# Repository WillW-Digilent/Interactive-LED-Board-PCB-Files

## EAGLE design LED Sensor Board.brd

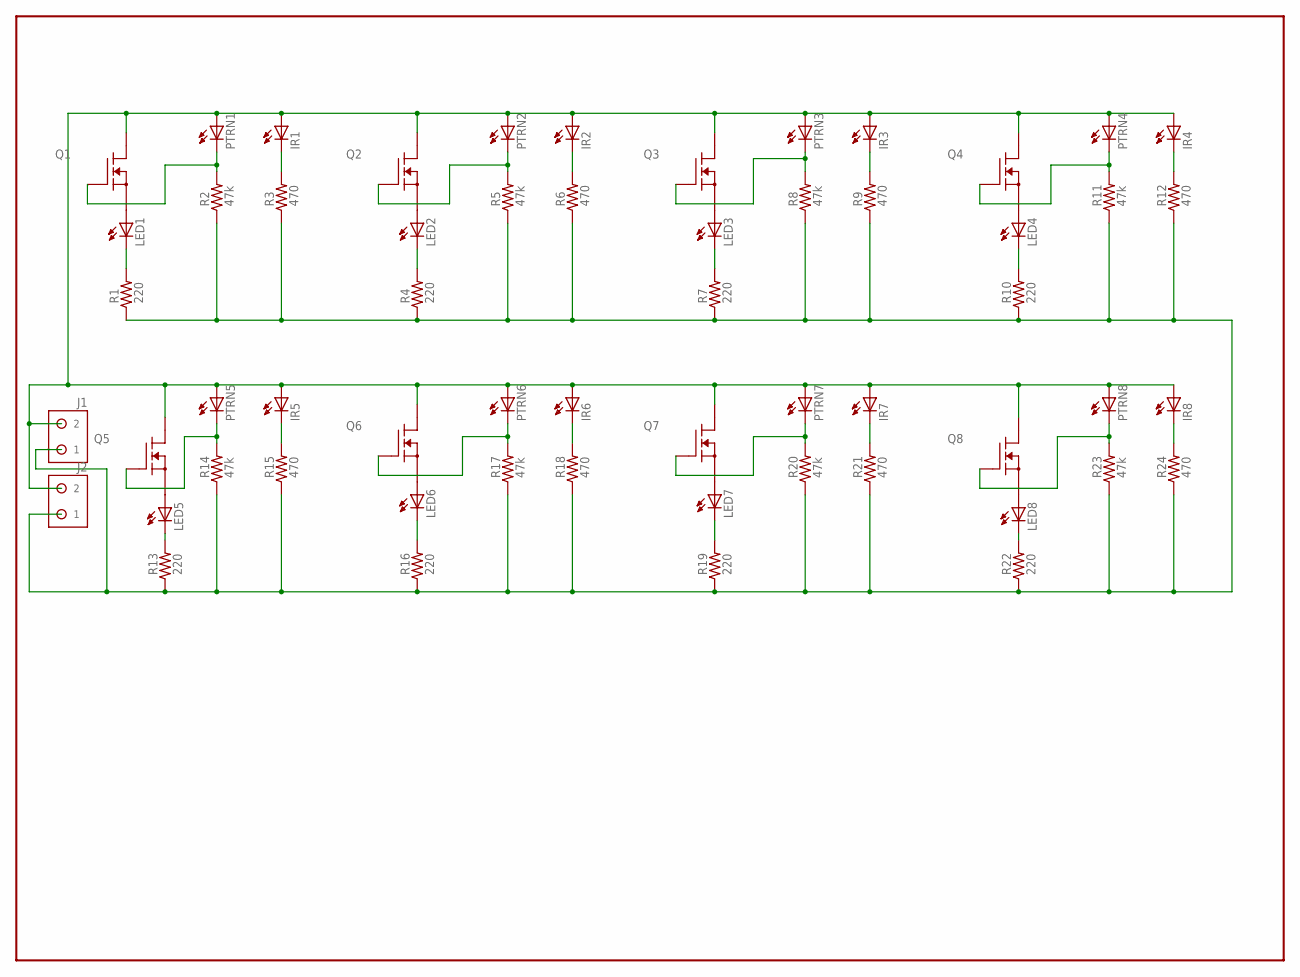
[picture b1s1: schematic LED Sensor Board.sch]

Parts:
IR1, IR2, IR3, IR4, IR5, IR6, IR7, IR8: LED-T1-3/4; LED-5MM
J1, J2: HDR-1X2
LED1, LED2, LED3, LED4, LED5, LED6, LED7, LED8: LED-T1-3/4; LED-5MM
PTRN1, PTRN2, PTRN3, PTRN4, PTRN5, PTRN6, PTRN7, PTRN8: LED-T1-3/4; LED-5MM
Q1, Q2, Q3, Q4, Q5, Q6, Q7, Q8: ZVN2110A; TO92-
R1, R4, R7, R10, R13, R16, R19, R22: 220; 0207/10
R2, R5, R8, R11, R14, R17, R20, R23: 47k; 0207/10
R3, R6, R9, R12, R15, R18, R21, R24: 470; 0207/10

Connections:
9VSUPPLY: IR1.A, IR2.A, IR3.A, IR4.A, IR5.A, IR6.A, IR7.A, IR8.A, J1.2, J2.2, PTRN1.A, PTRN2.A, PTRN3.A, PTRN4.A, PTRN5.A, PTRN6.A, PTRN7.A, PTRN8.A, Q1.1 (D), Q2.1 (D), Q3.1 (D), Q4.1 (D), Q5.1 (D), Q6.1 (D), Q7.1 (D), Q8.1 (D)
GND: J1.1, J2.1, R1.1, R2.1, R3.1, R4.1, R5.1, R6.1, R7.1, R8.1, R9.1, R10.1, R11.1, R12.1, R13.1, R14.1, R15.1, R16.1, R17.1, R18.1, R19.1, R20.1, R21.1, R22.1, R23.1, R24.1
unnamed: LED1.A, Q1.3 (S)
unnamed: LED1.K (C), R1.2
unnamed: PTRN1.K (C), Q1.2 (G), R2.2
unnamed: IR1.K (C), R3.2
unnamed: LED2.A, Q2.3 (S)
unnamed: LED2.K (C), R4.2
unnamed: PTRN2.K (C), Q2.2 (G), R5.2
unnamed: IR2.K (C), R6.2
unnamed: LED3.A, Q3.3 (S)
unnamed: LED3.K (C), R7.2
unnamed: PTRN3.K (C), Q3.2 (G), R8.2
unnamed: IR3.K (C), R9.2
unnamed: LED4.A, Q4.3 (S)
unnamed: LED4.K (C), R10.2
unnamed: PTRN4.K (C), Q4.2 (G), R11.2
unnamed: IR4.K (C), R12.2
unnamed: PTRN5.K (C), Q5.2 (G), R14.2
unnamed: IR5.K (C), R15.2
unnamed: LED8.A, Q8.3 (S)
unnamed: LED5.K (C), R13.2
unnamed: LED7.A, Q7.3 (S)
unnamed: LED6.K (C), R16.2
unnamed: PTRN6.K (C), Q6.2 (G), R17.2
unnamed: IR6.K (C), R18.2
unnamed: LED6.A, Q6.3 (S)
unnamed: LED7.K (C), R19.2
unnamed: PTRN7.K (C), Q7.2 (G), R20.2
unnamed: IR7.K (C), R21.2
unnamed: LED5.A, Q5.3 (S)
unnamed: LED8.K (C), R22.2
unnamed: PTRN8.K (C), Q8.2 (G), R23.2
unnamed: IR8.K (C), R24.2

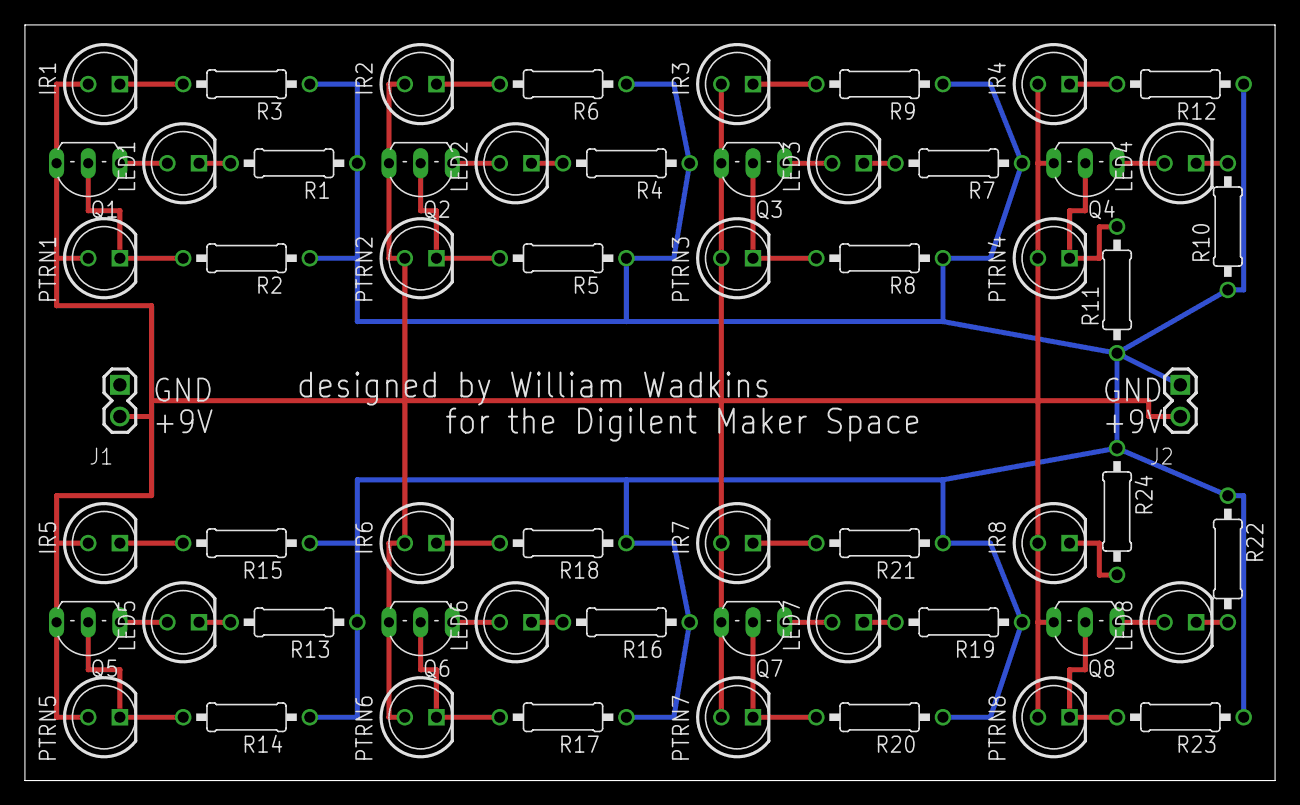
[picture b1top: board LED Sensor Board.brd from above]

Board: 2 copper layers, 100.3 x 60.6 mm, 58 parts (0 on the bottom side), 34 nets.

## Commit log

2014-06-09 All files to commit
